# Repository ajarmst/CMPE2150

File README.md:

# CMPE2150
Development for the Practical Electronics course

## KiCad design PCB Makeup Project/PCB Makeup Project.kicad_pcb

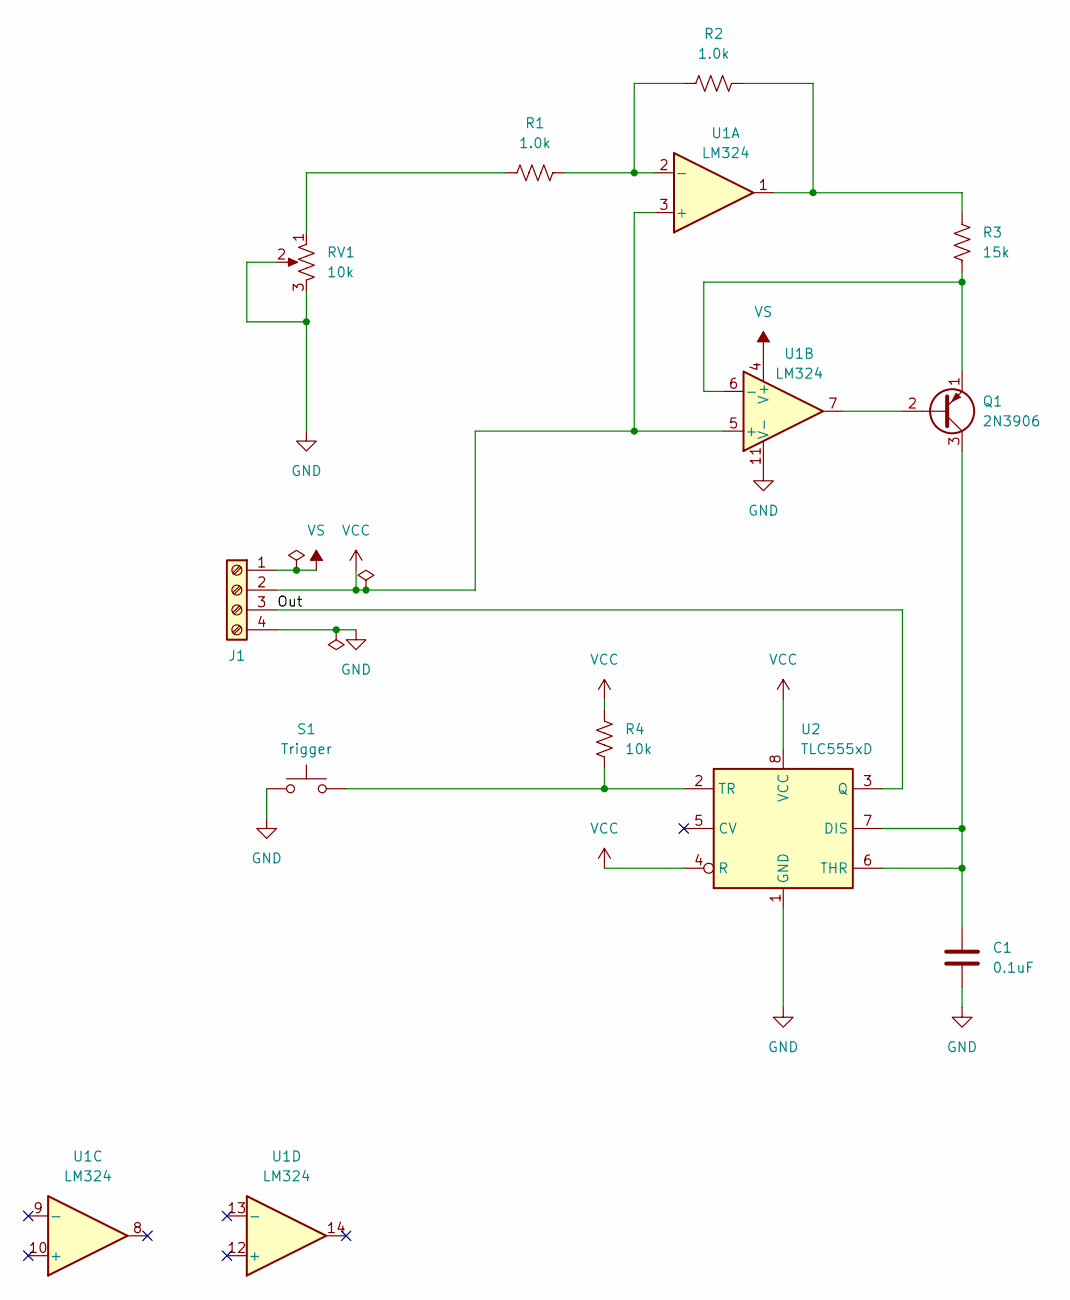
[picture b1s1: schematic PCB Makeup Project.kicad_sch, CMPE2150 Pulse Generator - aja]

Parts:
C1: 0.1uF; C_0805_2012Metric
J1: Screw_Terminal_01x04; TerminalBlock_MetzConnect_Type094_RT03504HBLU_1x04_P5.00mm_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
Q1: 2N3906; TO-92
R1, R2: 1.0k; R_0805_2012Metric
R3: 15k; R_0805_2012Metric
R4: 10k; R_0805_2012Metric
RV1: 10k; Potentiometer_Piher_PT-10-V10_Vertical
S1: Trigger; SW_PUSH_6mm
U1: LM324; TSSOP-14_4.4x5mm_P0.65mm
U2: TLC555xD; SOIC-8_3.9x4.9mm_P1.27mm

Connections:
/Out: J1.3, U2.3 (Q)
GND: C1.2, J1.4, RV1.2, RV1.3, S1.1, U1.11 (V-), U2.1 (GND)
unnamed: Q1.2 (B), U1.7
unnamed: C1.1, Q1.3 (C), U2.6 (THR), U2.7 (DIS)
unnamed: Q1.1 (E), R3.2, U1.6 (-)
unnamed: R1.2, RV1.1
unnamed: R2.1, R3.1, U1.1
unnamed: R1.1, R2.2, U1.2 (-)
unnamed: R4.2, S1.2, U2.2 (TR)
VCC: J1.2, R4.1, U1.3 (+), U1.5 (+), U2.4 (R), U2.8 (VCC)
VS: J1.1, U1.4 (V+)

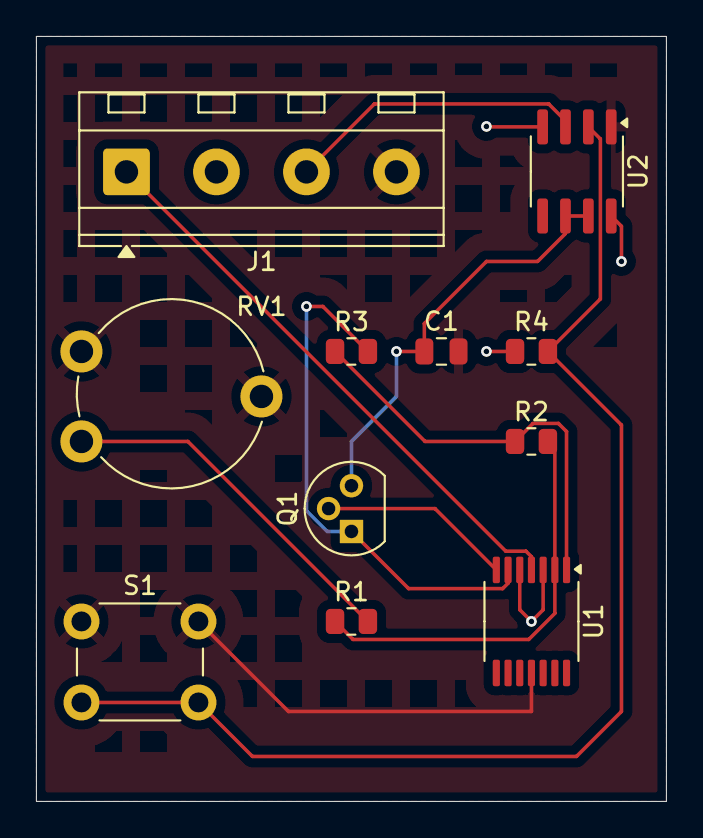
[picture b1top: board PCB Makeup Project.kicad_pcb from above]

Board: 2 copper layers, 35.0 x 42.5 mm, 11 parts (0 on the bottom side), 11 nets.

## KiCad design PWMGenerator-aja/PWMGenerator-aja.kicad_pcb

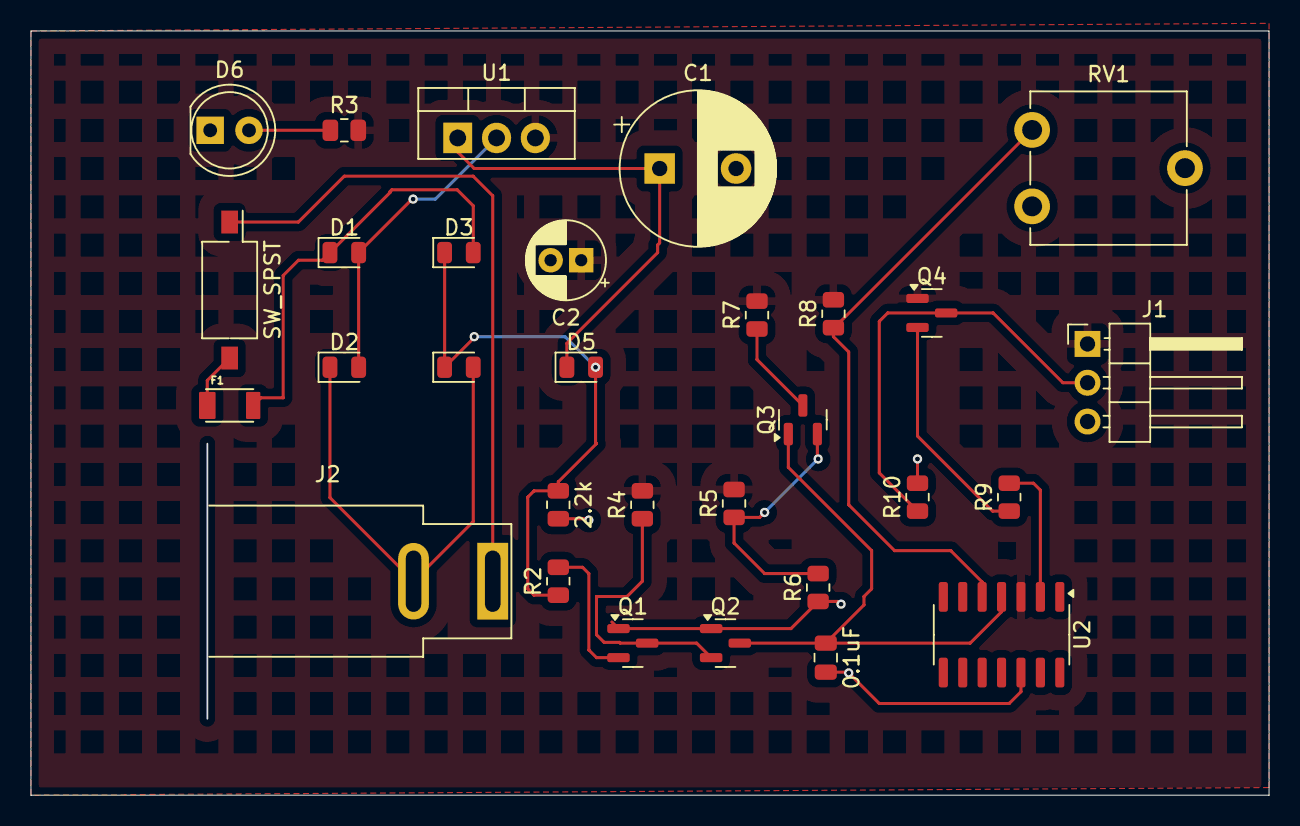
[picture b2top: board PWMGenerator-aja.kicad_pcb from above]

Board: 2 copper layers, 81.0 x 50.0 mm, 30 parts (0 on the bottom side), 18 nets.

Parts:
C1: 220uF; CP_Radial_D10.0mm_P5.00mm
C2: 10uF; CP_Radial_D5.0mm_P2.00mm
C3: 0.1uF; C_0805_2012Metric
D1, D2, D3, D4, D5: 1N4005G; D_0805_2012Metric
D6: LED; LED_D5.0mm
F1: NANOSMDC016F-2; RESC3115X65N
J1: Conn_01x03_Pin; PinHeader_1x03_P2.54mm_Horizontal
J2: Barrel_Jack; BarrelJack_SwitchcraftConxall_RAPC10U_Horizontal
Q1, Q2: 2N3904; SOT-23
Q3, Q4: 2N3906; SOT-23
R1, R8: 2.2k; R_0805_2012Metric
R2: 1M; R_0805_2012Metric
R3: 330; R_0805_2012Metric
R4: 10k; R_0805_2012Metric
R5: 220k; R_0805_2012Metric
R6: 390k; R_0805_2012Metric
R7: 22k; R_0805_2012Metric
R9: 8.2k; R_0805_2012Metric
R10: 180; R_0805_2012Metric
RV1: 5k; Potentiometer_ACP_CA9-V10_Vertical
SW1: SW_SPST; SW_DIP_SPSTx01_Slide_Omron_A6S-110x_W8.9mm_P2.54mm
U1: LM7805_TO220; TO-220-3_Vertical
U2: LM339; SOIC-14_3.9x8.7mm_P1.27mm

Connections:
GND: C1.2, C2.2, C3.2, D1.2 (A), D2.2 (A), D6.1 (K), J1.3, Q1.1 (E), Q2.1 (E), R1.2, R6.1, R10.2, RV1.1, RV1.2, U1.2 (GND), U2.12 (V-)
GNDPWR: D2.1 (K), D4.2 (A), J2.2
unnamed: D1.1 (K), D3.2 (A), F1.2
unnamed: D3.1 (K), D4.1 (K), D5.2 (A), R1.1, R2.1
unnamed: C1.1, D5.1 (K), U1.1 (VI)
unnamed: D6.2 (A), R3.1
unnamed: J1.2, Q4.3 (C), R10.1
unnamed: Q1.2 (B), R2.2
unnamed: Q1.3 (C), Q2.2 (B), R4.1
unnamed: C3.1, Q2.3 (C), Q3.1 (C), U2.4 (-)
unnamed: Q3.2 (B), R5.1, R6.2
unnamed: Q3.3 (E), R7.1
unnamed: Q4.2 (B), R9.1
unnamed: R9.2, U2.2
unnamed: J2.1, SW1.1 (A)
unnamed: R8.1, RV1.3, U2.5 (+)
VAC: F1.1, SW1.2 (B)
VCC: C2.1, J1.1, Q4.1 (E), R3.2, R4.2, R5.2, R7.2, R8.2, U1.3 (VO), U2.3 (V+)

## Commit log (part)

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2023-02-13 Starting Notes 6
    Electromechanics
2023-02-13 More work on notes
2023-02-13 Minor tweaks
2023-03-03 Added presentation on electromagnetic actuators
2024-09-13 Moving content to Quarto for BrightSpace (BS)
2024-09-13 Added SA03
2024-09-13 Added Notes 3 - Circuit Isolation
2024-09-17 Finish SA04, start Lab02
2024-09-17 Completed Lab 2
2024-09-18 Fixed broken left TOC by moving right.
2024-09-24 Finished Notes 4: relays and SSRs
2024-09-24 Started SA05
2024-09-24 Completed part 1 od SA05
2024-09-26 Finish SA05
2024-09-26 Completed Lab 03
2024-09-28 Reflowed document for Emacs
2024-09-29 Started work on Notes 5
2024-09-29 Working on margin figures. Not going well.
2024-09-30 Checkpoint
2024-09-30 Fixed major issue with margin figures.
2024-10-01 More work on Notes 5
2024-10-01 Cruft got in in last commit.
2024-10-01 Completed project 01
2024-10-01 Work on SCR part of notes
2024-10-01 Restore missing PDF render
2024-10-04 More work on AC Controller notes
2024-10-04 Finished Notes 5
2024-10-10 SA 06
2024-10-15 Added skeleton for heat notes.
2024-10-16 Started Notes 6
2024-10-17 More work on Notes 6. Added IEEE Biblio stuff
2024-10-17 Finished Notes 6
2024-10-17 Committing changes RStudio murdered for some reason
2024-10-18 New output
2024-10-18 Auto stash before merge of "main" and "origin/main"
2024-10-18 Whups. Sync first, dude. Fixed.
2024-10-18 Finished Project 4
2024-10-20 Finished SA 07
2024-10-20 Started Project 2
2024-10-21 Updated Project 2
2024-10-22 Nearly done Project 2
2024-10-22 Largely complete Project 2
2024-10-24 Initial part of Lab 5
2024-10-24 Lab 5 complete
2024-10-25 First skeleton for Notes 7, fooling around with Pandoc.
2024-10-25 Text content to Notes 7 ported
2024-10-25 Images from motor notes
2024-10-25 work on notes 7
2024-10-25 Notes 7 finished
2024-10-29 SA08 complete
2024-10-31 Notes 8 - Servomotors
2024-11-01 SA09 - Servo Motors
2024-11-07 Lab 6. Also some tweaks to code layout in quarto.
2024-11-15 Started on Stepper Notes
2024-11-15 Finished stepper notes
2024-11-19 SA10 - Steppers
2024-11-19 Don't need to track RHistory
2024-11-20 Lab 07 - Stepper
2024-11-22 Started encoder notes
2024-11-25 Update on Encoders (Notes 10)
2024-11-25 Finished off encoder stuff
2024-11-27 Project 3, which closes out the Motors unit
2024-12-02 Started LAB A
2024-12-03 Initial skeleton and intro
2024-12-04 Significant update to PCBPA. Added Kicad rev 0.1.
2024-12-04 Version 0.2 + finished PCB Project A
2024-12-08 Finished Schematic A
    Symbols and connections.
2024-12-08 Rev 0.4. Release version of A solution. Updated PCB Project A notes.
2024-12-09 Ready to start PCB Project B
2024-12-09 Resistors and diodes annotated.
2024-12-09 Well along in annotations.
2024-12-09 Getting there on PCB Project B.
2024-12-09 Done everything but three parts.
2024-12-09 All but barrel jack
2024-12-09 Version 0.6. Solution to B.
2024-12-09 Added pdf of solution
2024-12-10 Correcting minor error. Replace solution files.
2024-12-10 Starting component placement
2024-12-10 CSS tweaks for math font
2024-12-11 Work on component placement
2024-12-11 Initial placement
2025-01-02 No need to track backups
2025-01-08 Updated syllabus, convert notes 1 to new format.
2025-05-16 Started makeup PCB assignment design.
2025-05-16 Started new procedure writeup for PCB X
2025-05-16 Multisim Implementation
2025-05-16 work on writeup
2025-05-17 Yadda
2025-05-17 Whups. stop ignoring *.tex now that we're doing custom stuff.
2025-05-17 Completed Part 1 design
2025-05-17 Part 2 complete
2025-05-17 Document complete. First draft,
2026-01-14 Removed old PCB files
2026-01-21 Added Original SA 1,2; Lab 1
2026-01-21 Cleaning Up
2026-01-22 refactor(syllabus): Convert instructor and evaluation tables to pipe format
2026-01-22 refactor(syllabus): Adjust column width for Schedule table
2026-03-10 docs: Update syllabus tables to Quarto grid syntax
